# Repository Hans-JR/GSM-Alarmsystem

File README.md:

# GSM-Alarmsystem
Based on Arduino Nano and SIM800L

The system provides 3 inputs. One is used for an PIR detector.
This PIR sends a HIGH-Signal of a certain time and returnes to low if no motion is detected.
If the signal is retrigered, a new message is being sent.
The other two inputs issue a message, if the input goes from low to high. Only one message is being sent per event.
The tel number and the individual text has to be entered into the script prior compilation.
If a terminal is connected to the Arduino serial port, all transmitted messages will be displayed on the terminal. The baudrate is 9600.
A PCB and a simple housing are available (folder KiCad and Gehäuse)

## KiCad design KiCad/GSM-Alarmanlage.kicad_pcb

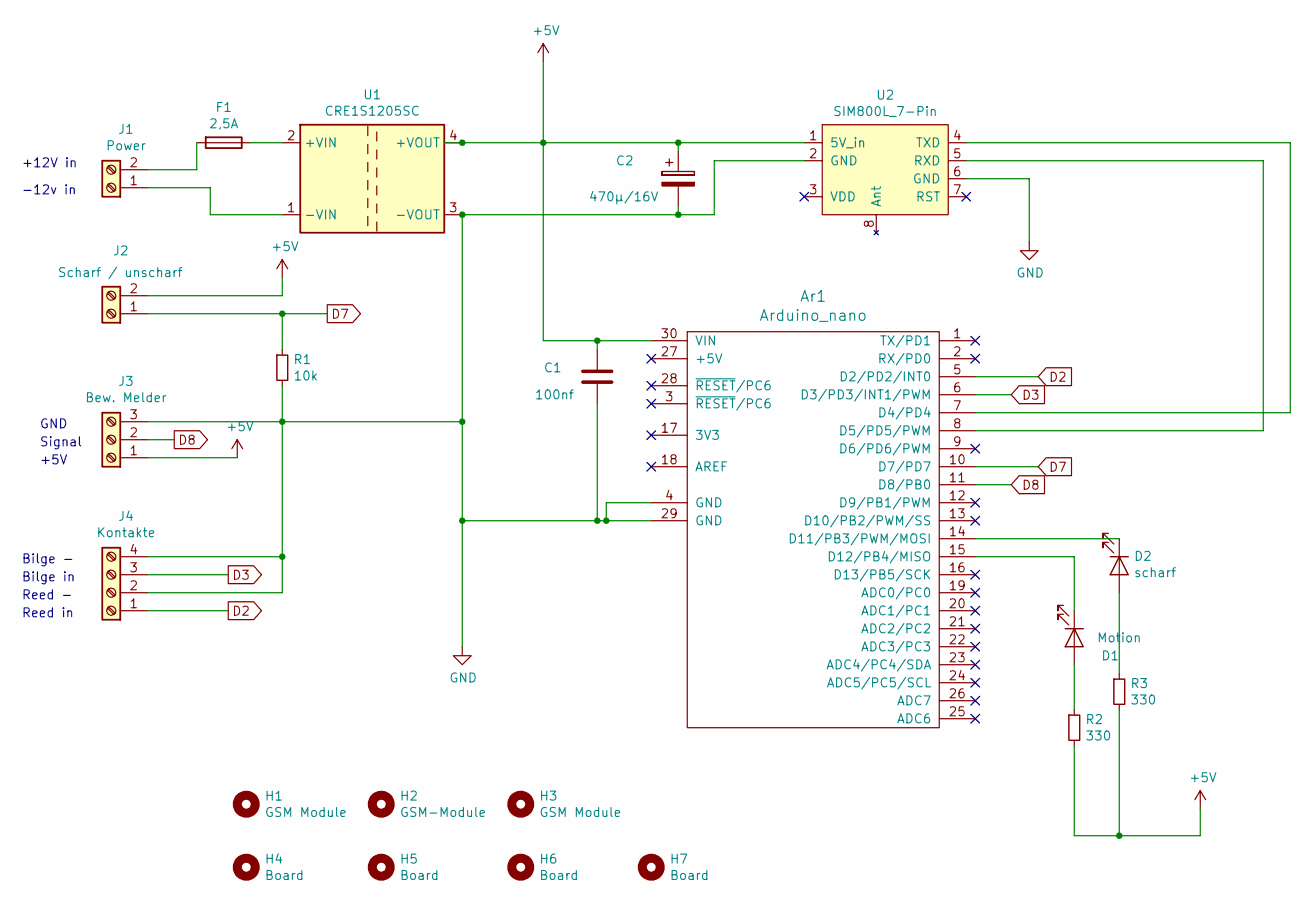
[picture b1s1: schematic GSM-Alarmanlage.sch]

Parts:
Ar1: Arduino_nano; ArduinoNano
C1: 100nf; C_Disc_D5.0mm_W2.5mm_P2.50mm
C2: 470µ/16V; CP_Radial_D8.0mm_P3.50mm
D1: Motion; LED_D5.0mm
D2: scharf; LED_D5.0mm
F1: 2,5A; Fuseholder_Cylinder-5x20mm_Stelvio-Kontek_PTF78_Horizontal_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
H1, H3: GSM Module; MountingHole_3.2mm_M3
H2: GSM-Module; MountingHole_3.2mm_M3
H4, H5, H6, H7: Board; MountingHole_3.2mm_M3
J1: Power; 250-202
J2: Scharf / unscharf; 250-202
J3: Bew. Melder; 250-203
J4: Kontakte; 250-204
R1: 10k; R_Axial_DIN0309_L9.0mm_D3.2mm_P12.70mm_Horizontal
R2, R3: 330; R_Axial_DIN0309_L9.0mm_D3.2mm_P12.70mm_Horizontal
U1: CRE1S1205SC; Converter_DCDC_LM2596S_Modul
U2: SIM800L_7-Pin

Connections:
+5V: Ar1.30 (VIN), C1.1, C2.1, J2.2, J3.1, R2.2, R3.2, U1.4 (+VOUT), U2.1 (5V_in)
D2: Ar1.5 (D2/PD2/INT0), J4.1
D3: Ar1.6 (D3/PD3/INT1/PWM), J4.3
D7: Ar1.10 (D7/PD7), J2.1, R1.1
D8: Ar1.11 (D8/PB0), J3.2
GND: Ar1.4 (GND), Ar1.29 (GND), C1.2, C2.2, J3.3, J4.2, J4.4, R1.2, U1.3 (-VOUT), U2.2 (GND), U2.6 (GND)
unnamed: Ar1.7 (D4/PD4), U2.4 (TXD)
unnamed: Ar1.8 (D5/PD5/PWM), U2.5 (RXD)
unnamed: Ar1.14 (D11/PB3/PWM/MOSI), D2.1 (K)
unnamed: Ar1.15 (D12/PB4/MISO), D1.1 (K)
unnamed: D1.2 (A), R2.1
unnamed: D2.2 (A), R3.1
unnamed: F1.1, U1.2 (+VIN)
unnamed: F1.2, J1.2
unnamed: J1.1, U1.1 (-VIN)

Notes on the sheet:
+12V in
-12v in
GND
Signal
+5V
Bilge -
Bilge in
Reed -
Reed in

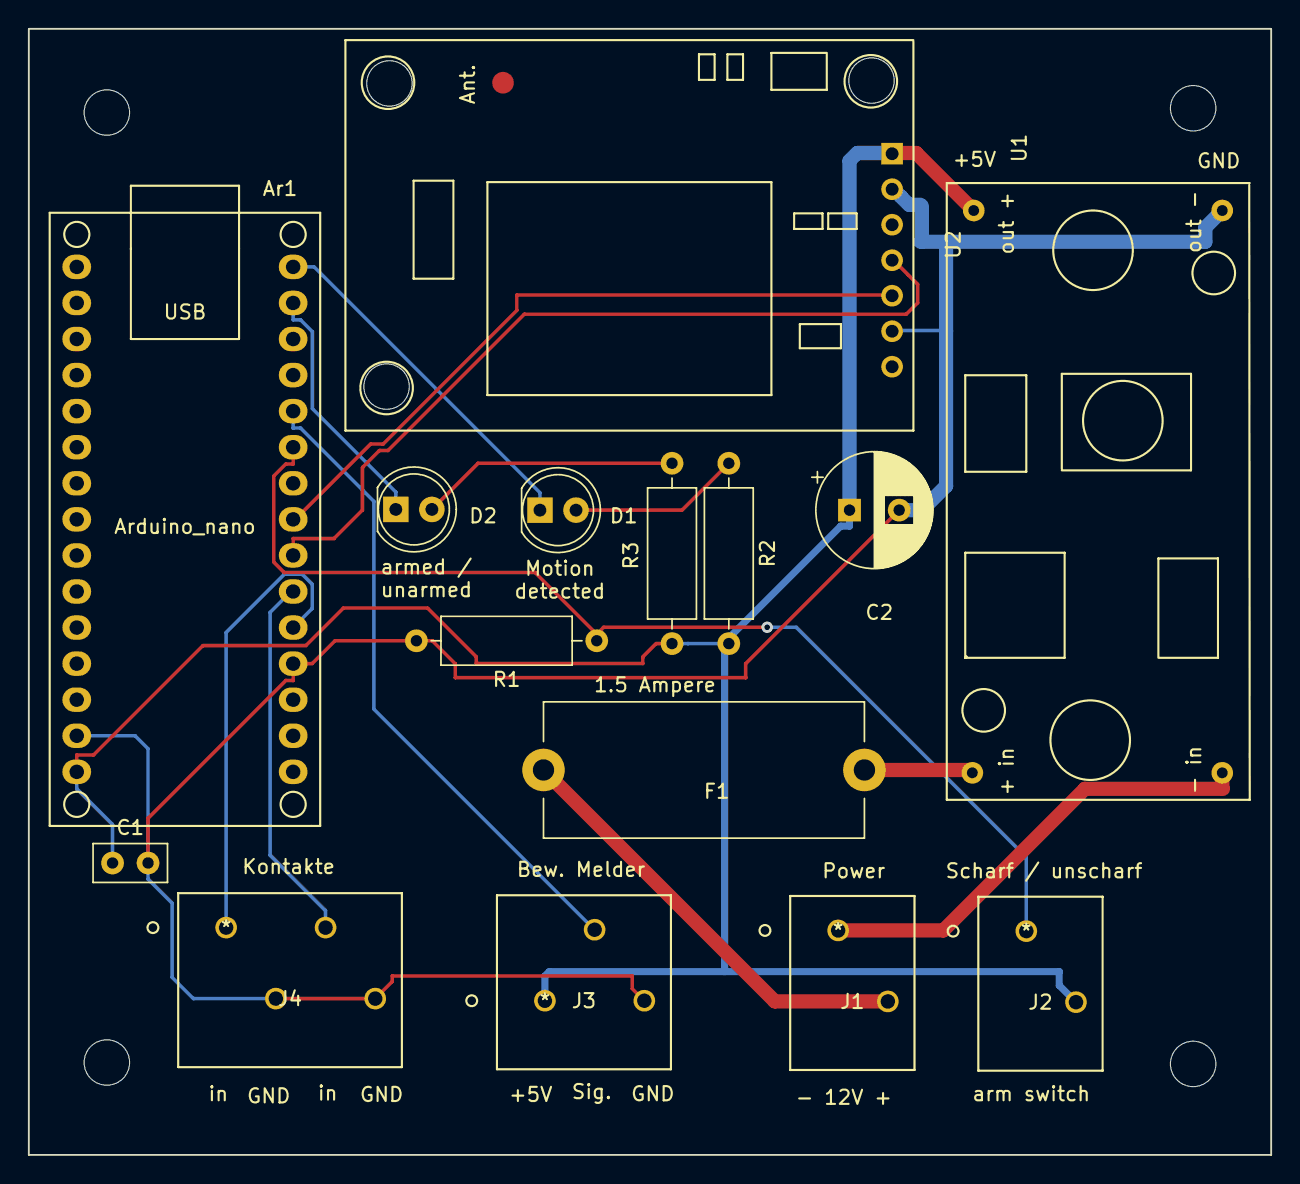
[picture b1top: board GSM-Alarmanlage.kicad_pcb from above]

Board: 2 copper layers, 87.5 x 79.3 mm, 22 parts (0 on the bottom side), 15 nets.

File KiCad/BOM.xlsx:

BOM for GSM Alarmsystem
 | Ref. Nr. | Bezeichnung | Artikel Nr. (Reichelt) | Link
 | C1 | 100nf | KERKO 100N | Keramik-Scheibenkondensatoren bei reichelt elektronik
 | C2 | 470µf/16V | RAD 220/16 | Elektrolytkondensatoren, radiale Bauform und SMD-Elkos bei reichelt elektronik
 | D1 | LED grün | LED 5MM GN | LED 5MM GN: LED, 5 mm, bedrahtet, grün, 18 mcd, 60° bei reichelt elektronik
 | D2 | LED rot | LED 5MM RT | LED 5MM RT: LED, 5 mm, bedrahtet, rot, 4,5 mcd, 60° bei reichelt elektronik
 | F1 | Si 1,5A | PL 112000 | PL 112000: Sicherungshalter, Feinsicherungen 5x20mm, max. 6,3A - 250V bei reich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
 | J1 | Connector WAGO 250:250-202 | WAGO 250-202 | WAGO 250-202: Klemmleiste mit Betätigungsdrückern, RM 3,5 mm, 8A, 2-pol bei rei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
 | J2 | Connector WAGO 250:250-202 | WAGO 250-202 | WAGO 250-202: Klemmleiste mit Betätigungsdrückern, RM 3,5 mm, 8A, 2-pol bei rei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
 | J3 | Connector WAGO 250:250-203 | WAGO 250-203 | WAGO 250-203: Klemmleiste mit Betätigungsdrückern, RM 3,5 mm, 8A, 3-pol bei rei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
 | J4 | Connector WAGO 250:250-204 | WAGO 250-204 | WAGO 250-204: Klemmleiste mit Betätigungsdrückern, RM 3,5 mm, 8A, 4-pol bei rei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
 | R1 | 10k | VI MBB0207VD1002 | VI MBB0207VD1002: Dünnschichtwiderstand, axial, 0,11 W, 10 kOhm, 0,1% bei reich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
 | R2 | 330 | VI MBA02040C3300 | VI MBA02040C3300: Dünnschichtwiderstand, axial, 0,4 W, 330 Ohm, 1% bei reichelt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
 | R3 | 330 | VI MBA02040C3300 | VI MBA02040C3300: Dünnschichtwiderstand, axial, 0,4 W, 330 Ohm, 1% bei reichelt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
 | U1 | LM2596S DC-DC Netzteil Adapter Step down Modul für Arduino | AZ-Delivery | LM2596S DC-DC Netzteil Adapter Step down Modul für Arduino – AZ-Delivery
 | U2 | SIM800L V2.0 Quad Band GSM GPRS Modul | Makershop | SIM800L V2.0 Quad Band GSM GPRS Modul Antenne Adapter Arduino Raspberry Pi | eB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
 | U3 | Arduino Nano | AZ-Delivery | Nano V3.0 mit Atmega328 CH340! 100% Arduino kompatibel mit Nano V3 – AZ-Delivery

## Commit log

2021-05-05 Create LICENSE

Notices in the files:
KiCad/GSM-Alarmanlage.kicad_pcb:
CC BY-NC-SA
parts and their libraries:
Copyright 2016 Accelerated Designs. All rights reserved.
